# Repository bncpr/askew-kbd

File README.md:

# askew-kbd
Custom split keyboard, inspired by crkbd by foostan.

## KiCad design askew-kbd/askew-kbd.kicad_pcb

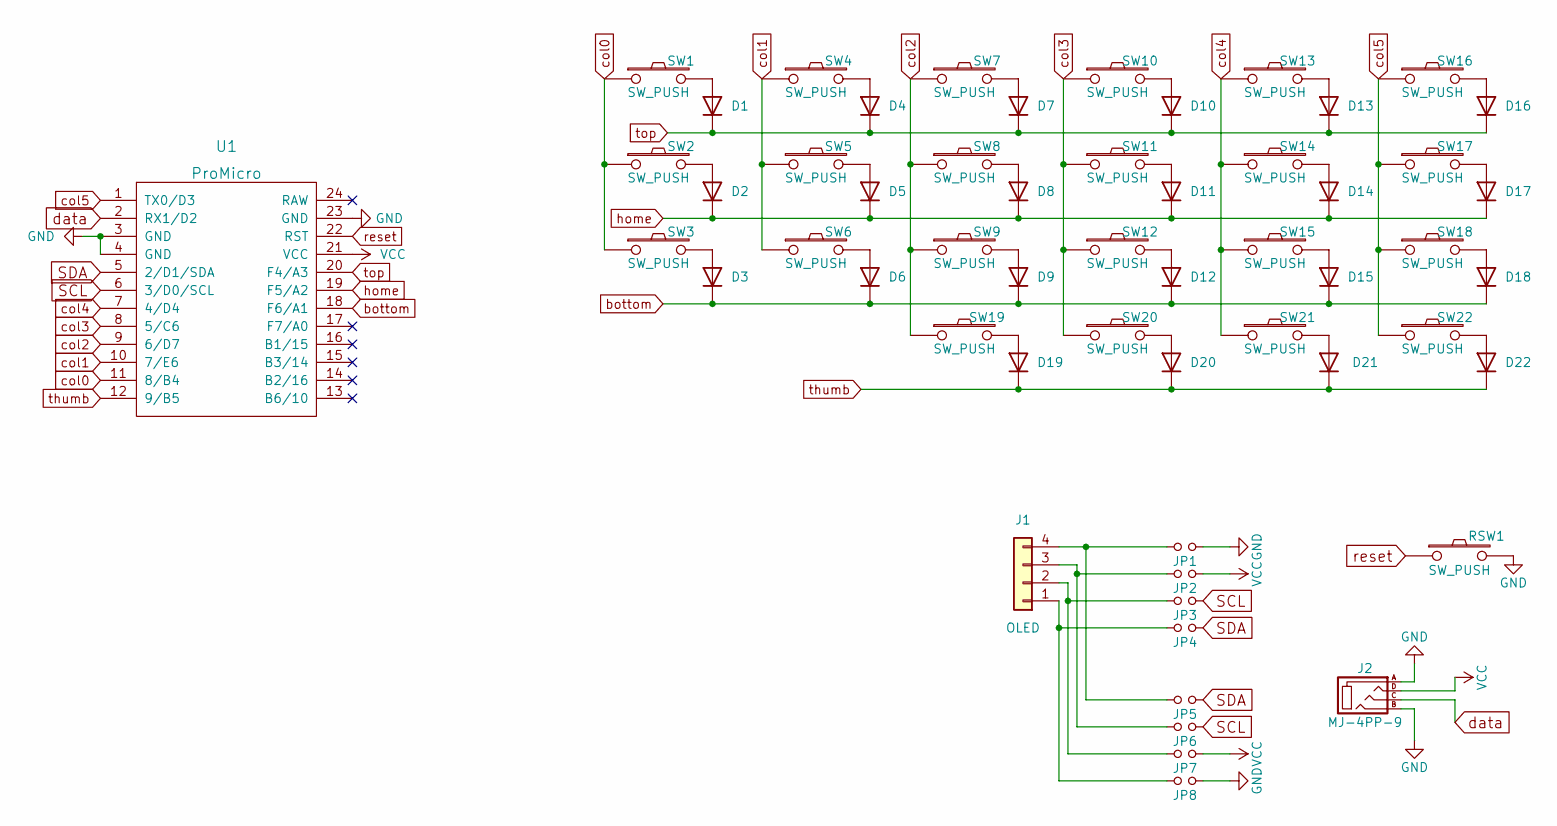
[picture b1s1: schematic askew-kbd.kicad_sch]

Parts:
D1, D2, D3, D4, D5, D6, D7, D8, D9, D10, D11, D12, D13, D14, D15, D16, D17, D18, D19, D20, D21, D22: DIODE; D3_TH_SMD
J1: OLED; OLED_v2
J2: MJ-4PP-9
JP1, JP2, JP3, JP4, JP5, JP6, JP7, JP8: Jumper
RSW1: SW_PUSH; ResetSW
SW1, SW2, SW3, SW4, SW5, SW6, SW7, SW8, SW9, SW10, SW11, SW12, SW13, SW14, SW15, SW16, SW17, SW18, SW21: SW_PUSH; ChocV1_V2_Hotswap_reversed_choc_spacing
SW19, SW20, SW22: SW_PUSH; ChocV1_V2_Hotswap_reversed_15u_choc_spacing
U1: ProMicro; ProMicro_unrouted_type_c

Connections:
GND: J2.A, J2.B, JP1.1, JP8.1, RSW1.2, U1.3 (GND), U1.4 (GND), U1.23 (GND)
unnamed: D1.1 (A), SW1.2
unnamed: D2.1 (A), SW2.2
unnamed: D3.1 (A), SW3.2
unnamed: D4.1 (A), SW4.2
unnamed: D5.1 (A), SW5.2
unnamed: D6.1 (A), SW6.2
unnamed: D7.1 (A), SW7.2
unnamed: D8.1 (A), SW8.2
unnamed: D9.1 (A), SW9.2
unnamed: D10.1 (A), SW10.2
unnamed: D11.1 (A), SW11.2
unnamed: D12.1 (A), SW12.2
unnamed: D13.1 (A), SW13.2
unnamed: D14.1 (A), SW14.2
unnamed: D15.1 (A), SW15.2
unnamed: D16.1 (A), SW16.2
unnamed: D17.1 (A), SW17.2
unnamed: D18.1 (A), SW18.2
unnamed: D19.1 (A), SW19.2
unnamed: D20.1 (A), SW20.2
unnamed: D21.1 (A), SW21.2
unnamed: D22.1 (A), SW22.2
unnamed: J1.1, JP4.2, JP8.2
unnamed: J1.2, JP3.2, JP7.2
unnamed: J1.3, JP2.2, JP6.2
unnamed: J1.4, JP1.2, JP5.2
SCL: JP3.1, JP6.1, U1.6 (3/D0/SCL)
SDA: JP4.1, JP5.1, U1.5 (2/D1/SDA)
VCC: J2.D, JP2.1, JP7.1, U1.21 (VCC)
bottom: D3.2 (K), D6.2 (K), D9.2 (K), D12.2 (K), D15.2 (K), D18.2 (K), U1.18 (F6/A1)
col0: SW1.1, SW2.1, SW3.1, U1.11 (8/B4)
col1: SW4.1, SW5.1, SW6.1, U1.10 (7/E6)
col2: SW7.1, SW8.1, SW9.1, SW19.1, U1.9 (6/D7)
col3: SW10.1, SW11.1, SW12.1, SW20.1, U1.8 (5/C6)
col4: SW13.1, SW14.1, SW15.1, SW21.1, U1.7 (4/D4)
col5: SW16.1, SW17.1, SW18.1, SW22.1, U1.1 (TX0/D3)
data: J2.C, U1.2 (RX1/D2)
home: D2.2 (K), D5.2 (K), D8.2 (K), D11.2 (K), D14.2 (K), D17.2 (K), U1.19 (F5/A2)
reset: RSW1.1, U1.22 (RST)
thumb: D19.2 (K), D20.2 (K), D21.2 (K), D22.2 (K), U1.12 (9/B5)
top: D1.2 (K), D4.2 (K), D7.2 (K), D10.2 (K), D13.2 (K), D16.2 (K), U1.20 (F4/A3)

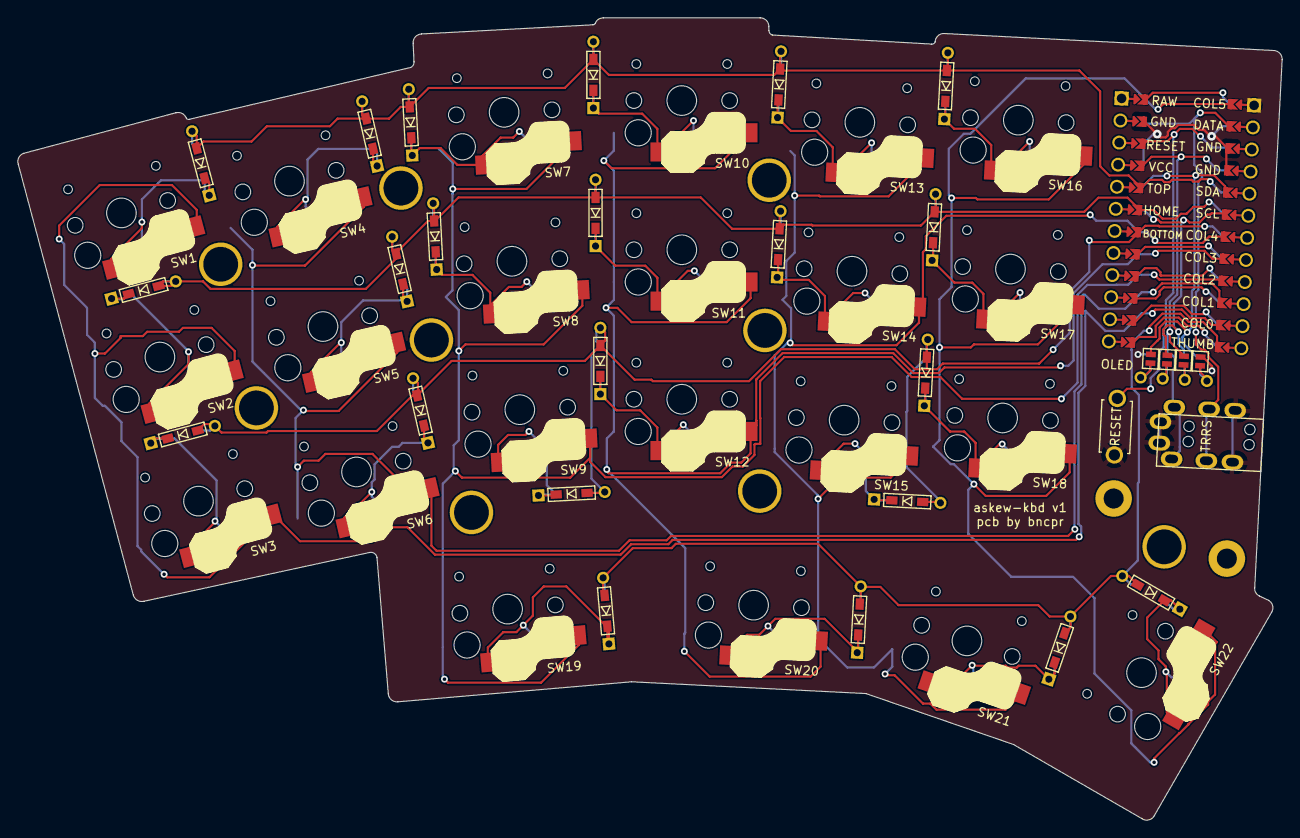
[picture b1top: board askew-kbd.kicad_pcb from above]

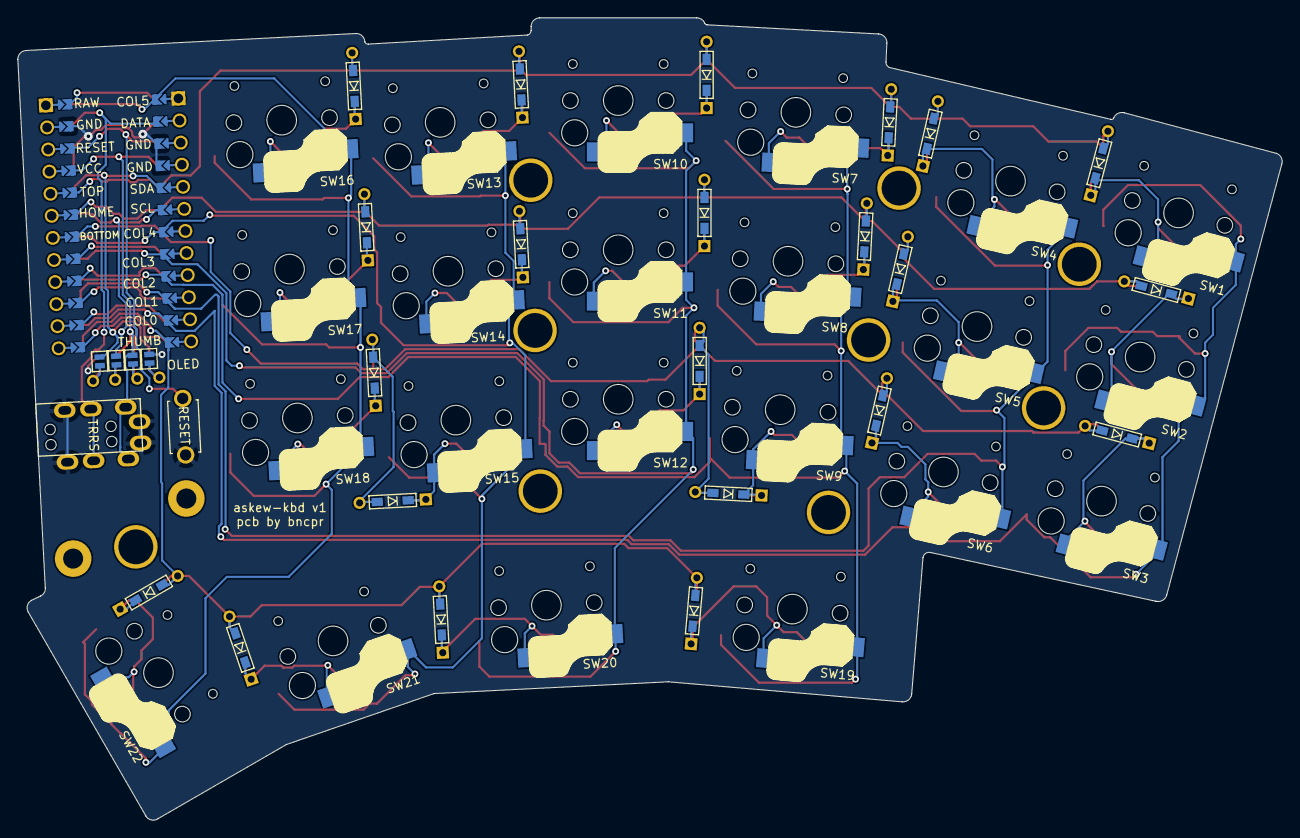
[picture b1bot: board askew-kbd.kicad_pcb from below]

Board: 2 copper layers, 145.2 x 92.1 mm, 58 parts (4 on the bottom side), 42 nets.

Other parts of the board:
H1: oled_cover_1; M2_Hole_TH
H2: oled_cover_2; M2_Hole_TH

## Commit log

2022-12-30 init
2022-12-31 unrouted base
2022-12-31 trrs and reset switch
2022-12-31 outline
2023-01-01 add breadcrumbs for far pinky
2023-01-01 led footprints
2023-01-02 mounting holes
2023-01-04 buzzer
2023-01-15 remove buzzer and add diodes silk
2023-01-17 add rotary
2023-01-17 promicro routing
2023-01-24 choc_spacing
2023-01-25 redo layout
2023-01-26 pro micro and diodes
2023-01-28 basic routing
2023-01-28 routing
2023-01-28 routing finished
2023-01-28 plates
2023-02-11 fix mcu silkscreen
2023-02-22 olep protector wip
2023-02-22 assets
2023-02-22 move assets
2023-04-13 readme
2023-09-20 oled protector wip
2023-09-27 3d case
